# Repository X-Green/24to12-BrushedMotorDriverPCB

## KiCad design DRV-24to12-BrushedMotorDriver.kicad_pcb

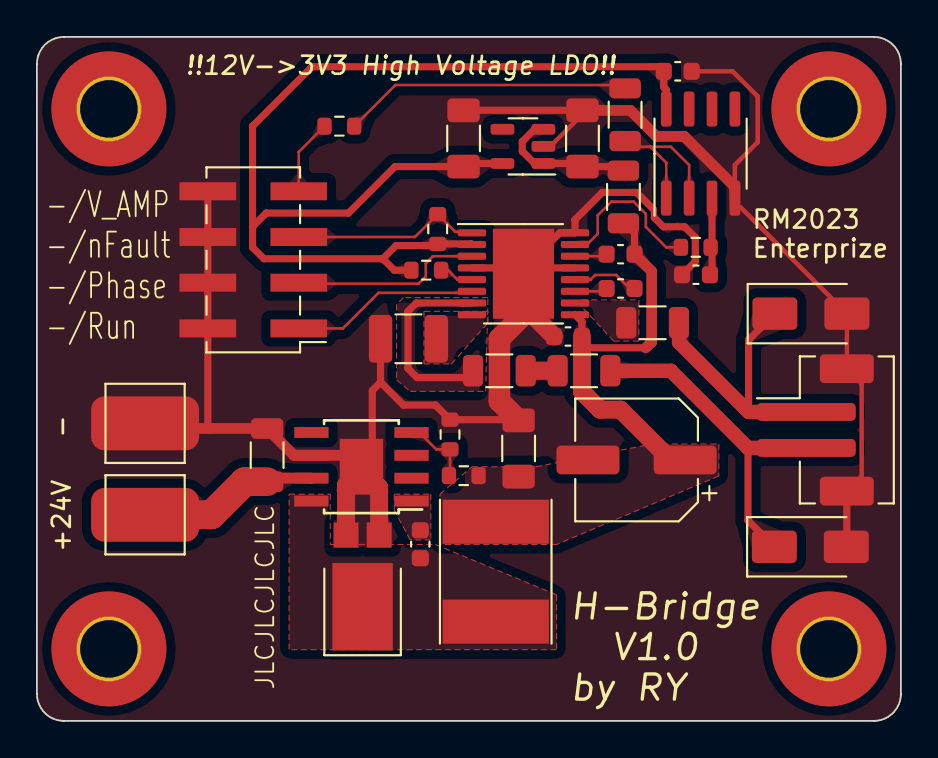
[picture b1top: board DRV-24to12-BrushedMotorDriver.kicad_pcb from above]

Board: 2 copper layers, 48.0 x 38.0 mm, 39 parts (0 on the bottom side), 26 nets.

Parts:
C1: 1nF; C_0603_1608Metric
C2, C3, C4: 100nF 50V; C_0603_1608Metric
C5, C9, C10: 2.2uF; C_1206_3216Metric_Pad1.33x1.80mm_HandSolder
C6: 22uF; C_1206_3216Metric
C7, C8: 10nF; C_0603_1608Metric
C11: 100uF 25V; CP_Elec_6.3x7.7
D1: D_Schottky; D_PowerDI-5
D2, D3: SS34; D_SMA
H1, H2, H3, H4: MountingHole_Pad; MountingHole_3.2mm_M3_Pad_TopOnly
J1: Conn_01x02; JST_PH_B2B-PH-SM4-TB_1x02-1MP_P2.00mm_Vertical
J3: Conn_02x04_Odd_Even; PinHeader_2x04_P2.54mm_Vertical_SMD
L1: 33uH; L_Taiyo-Yuden_NR-60xx_HandSoldering
R1, R2: 4.7K; R_0603_1608Metric
R3: 10K; R_0603_1608Metric
R4: 1.13K; R_0603_1608Metric
R5, R6, R7, R10: 0R 1A; R_1206_3216Metric
R8: 22R; R_0603_1608Metric
R9: 0R; R_1206_3216Metric
R_SENSE1: 500mR; R_1210_3225Metric_Pad1.30x2.65mm_HandSolder
R_VPROPI1: 100K; R_0603_1608Metric
TP1: PWR_IN+; TestPoint_Pad_4.0x4.0mm
TP2: PWR_IN-; TestPoint_Pad_4.0x4.0mm
U1: DRV8801PWP; HTSSOP-16-1EP_4.4x5mm_P0.65mm_EP3.4x5mm_Mask2.46x2.31mm
U2: TPS5430DDA; TI_SO-PowerPAD-8
U3: ME6214C33M5G; SOT-23-5
U4: LM358; SOIC-8_3.9x4.9mm_P1.27mm

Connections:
+3V3: C5.2, C8.2, R1.2, R2.1, U1.2 (MODE1), U3.5 (OUT), U4.8 (V+)
+12V: C3.1, C4.2, C9.2, C11.1, L1.2, R3.1, R10.1, U1.9 (VBB)
+24V: C6.1, TP1.1, U2.7 (VIN)
/DCDC_VSENSE: R3.2, R4.1, U2.4 (VSENSE)
/MOTOR+: D2.1 (K), J1.2, R7.2
/MOTOR-: D3.1 (K), J1.1, R5.2
/MOTOR_RUN: J3.1, U1.6 (ENABLE)
/NFAULT: J3.5, R1.1, U1.1 (~FAULT)
/PHASE_CTRL: J3.3, U1.3 (PHASE)
/VPROPI: C1.1, R_VPROPI1.2, U4.3 (+)
/VPROPI_AMP: J3.7, R8.2
GND: C1.2, C4.1, C5.1, C6.2, C8.1, C9.1, C10.1, C11.2, D1.2 (A), D2.2 (A), D3.2 (A), J1.MP (MountPin), J3.2, J3.4, J3.6, J3.8, R4.2, R_SENSE1.2, TP2.1, U1.4 (GND), U1.13 (GND), U1.16 (MODE2), U1.17 (GND(PPAD)), U2.6 (GND), U2.9 (GNDPAD), U3.2 (GND), U4.4 (V-)
unnamed: C7.2, D1.1 (K), L1.1, U2.8 (PH)
unnamed: R6.2, R7.1
unnamed: R8.1, R9.2
unnamed: C2.1, U1.11 (CP1)
unnamed: C2.2, U1.12 (CP2)
unnamed: R6.1, U1.7 (OUT+)
unnamed: R5.1, U1.10 (OUT-)
unnamed: R_SENSE1.1, U1.8 (SENSE)
unnamed: C3.2, U1.14 (VCP)
unnamed: R_VPROPI1.1, U1.15 (VPROPI)
unnamed: R2.2, U1.5 (~SLEEP)
unnamed: C7.1, U2.1 (BOOT)
unnamed: C10.2, R10.2, U3.1 (IN), U3.3 (EN)
unnamed: R9.1, U4.1, U4.2 (-)

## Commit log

2023-04-25 init Schemetic done
2023-04-25 gitignore
2023-04-26 Layout done
2023-04-26 ignore cache
2023-04-26 layout2
2023-04-26 ver1.0 done
